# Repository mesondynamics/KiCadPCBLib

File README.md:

# KiCadPCBLib
PCB library for KiCad: custom symbols and footprints

Remember to set up [KiCadPCBLib3dmodels](https://github.com/mesondynamics/KiCadPCBLib3dmodels) for custom 3d models.

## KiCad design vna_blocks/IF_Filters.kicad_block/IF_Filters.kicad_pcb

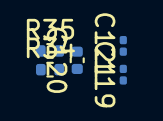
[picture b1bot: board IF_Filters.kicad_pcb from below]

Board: 8 copper layers, 5 parts (5 on the bottom side), 3 nets, no tracks yet.

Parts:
C119, C121: 10p; C_0201_0603Metric
C120: 27p; C_0402_1005Metric
R34, R35: 49.9; R_0402_1005Metric

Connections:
/RCVR1_IFF_N: C120.2, C121.1, R35.2
/RCVR1_IFF_P: C119.2, C120.1, R34.2
GNDA: C119.1, C121.2

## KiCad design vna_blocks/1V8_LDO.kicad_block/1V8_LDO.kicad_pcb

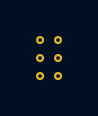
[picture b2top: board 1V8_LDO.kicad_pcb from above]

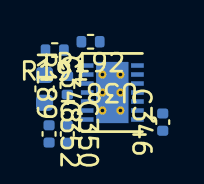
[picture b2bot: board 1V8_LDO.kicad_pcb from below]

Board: 8 copper layers, 8 parts (8 on the bottom side), 5 nets, no tracks yet.

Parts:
C346, C350, C352: 10u; C_0402_1005Metric
C348: 4.7u; C_0603_1608Metric
R189: 18k; R_0402_1005Metric
R191: 43k; R_0402_1005Metric
R192: 10k; R_0402_1005Metric
U38: LT3041ADE-PBF; 05-08-1708_ADI-L

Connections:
/1V8ADC1: C350.1, C352.1, R191.2, U38.12 (OUTS), U38.13 (OUT), U38.14 (OUT)
/Power/1V8/PGFB_1V8ADC1: R191.1, R192.2, U38.8 (PGFB)
/Power/3V8_int: C346.2, U38.1 (IN), U38.2 (IN), U38.3 (IN)
GNDA: C346.1, C348.2, C350.2, C352.2, R189.1, R192.1, U38.10 (GND), U38.11 (GND), U38.15 (GND)
unnamed: C348.1, R189.2, U38.9 (SET)

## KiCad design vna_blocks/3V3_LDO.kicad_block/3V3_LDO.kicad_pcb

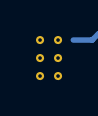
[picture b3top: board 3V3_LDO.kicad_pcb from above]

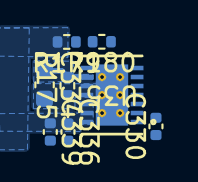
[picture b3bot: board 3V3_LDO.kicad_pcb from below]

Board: 8 copper layers, 8 parts (8 on the bottom side), 5 nets.

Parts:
C330, C336, C339: 10u; C_0402_1005Metric
C334: 4.7u; C_0603_1608Metric
R175: 33.2k; R_0402_1005Metric
R179: 89k; R_0402_1005Metric
R180: 10k; R_0402_1005Metric
U35: LT3041ADE-PBF; 05-08-1708_ADI-L

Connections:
/3V3_Synth: C336.1, C339.1, R179.2, U35.12 (OUTS), U35.13 (OUT), U35.14 (OUT)
/Power/3V3/PGFB_3V3Synth: R179.1, R180.2, U35.8 (PGFB)
GNDA: C330.1, C334.2, C336.2, C339.2, R175.1, R180.1, U35.10 (GND), U35.11 (GND), U35.15 (GND)
unnamed: C330.2, U35.1 (IN), U35.2 (IN), U35.3 (IN)
unnamed: C334.1, R175.2, U35.9 (SET)

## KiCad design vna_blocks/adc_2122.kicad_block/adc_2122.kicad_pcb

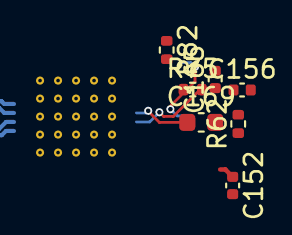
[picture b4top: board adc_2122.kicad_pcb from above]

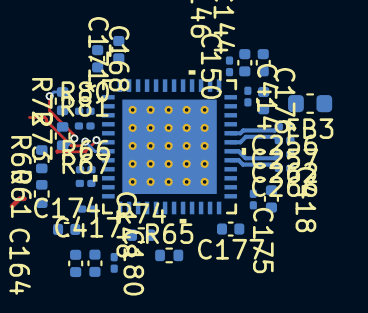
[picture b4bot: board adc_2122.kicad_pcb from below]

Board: 8 copper layers, 38 parts (31 on the bottom side), 24 nets.

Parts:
C144: 10u; C_0402_1005Metric
C146: 1u; C_0402_1005Metric
C148, C152, C156, C164, C165, C168, C171, C174, C175, C176, C177: 0.1u; C_0402_1005Metric
C150, C180, C414, C417, C418: 10p; C_0201_0603Metric
C169: 2.2u; C_0603_1608Metric
C256, C257, C262, C266: 0.1u; C_0201_0603Metric
FB3: MPZ1608S601ATA00; L_0603_1608Metric
R60, R61, R72, R73: 200; R_0402_1005Metric
R62, R75: 10; R_0402_1005Metric
R65, R74: 100; R_0402_1005Metric
R66, R67, R80, R81: 5; R_0201_0603Metric
R82: 1k; R_0402_1005Metric
U15: LTC2122IUK-TRPBF; QFN-48_UK_LIT-L

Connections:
/1V8_IO: C175.1, C176.1, C414.1, C418.1, U15.25 (OVDD), U15.26 (OVDD), U15.35 (OVDD), U15.36 (OVDD)
/ADC1_CLK_N: R74.2, U15.16 (DEVCLK+)
/ADC1_CLK_P: R74.1, U15.15 (DEVCLK-)
/Detector_adc_stage/1V8A_ADC1: C144.1, C146.1, C148.1, C150.1, C164.2, C168.2, C171.1, C174.2, C177.2, C180.1, C417.1, FB3.2, R82.1, U15.1 (VDD), U15.12 (VDD), U15.13 (VDD), U15.23 (VDD), U15.24 (VDD), U15.37 (VDD), U15.38 (VDD), U15.48 (VDD)
/Detector_adc_stage/A+: C256.2, U15.32 (CMLOUT_A0+)
/Detector_adc_stage/A-: C257.2, U15.31 (CMLOUT_A0-)
/Detector_adc_stage/B+: C262.2, U15.30 (CMLOUT_B0+)
/Detector_adc_stage/B-: C266.2, U15.29 (CMLOUT_B0-)
/Detector_adc_stage/SENSE: R82.2, U15.5 (SENSE)
/Detector_adc_stage/V_CM1: C165.1, R62.2, R75.2, U15.7 (VCM)
/RCVR1_IFF_N: R60.1, R66.1
/RCVR1_IFF_P: R61.2, R67.1
/RCVR1_IFR_N: R72.1, R80.1
/RCVR1_IFR_P: R73.2, R81.1
/SYSREF1_N: R65.2, U15.19 (SYSREF-)
/SYSREF1_P: R65.1, U15.18 (SYSREF+)
GNDA: C144.2, C146.2, C148.2, C150.2, C152.2, C156.2, C164.1, C165.2, C168.1, C169.2, C171.2, C174.1, C175.2, C176.2, C177.1, C180.2, C414.2, C417.2, C418.2, U15.2 (GND), U15.8 (GND), U15.11 (GND), U15.14 (GND), U15.17 (GND), U15.20 (GND), U15.39 (GND), U15.40 (GND), U15.47 (GND), U15.49 (GND)
unnamed: C152.1, R60.2, R61.1, R62.1
unnamed: C156.1, R72.2, R73.1, R75.1
unnamed: R80.2, U15.3 (AINA+)
unnamed: R81.2, U15.4 (AINA-)
unnamed: R67.2, U15.10 (AINB+)
unnamed: R66.2, U15.9 (AINB-)
unnamed: C169.1, U15.6 (VREF)

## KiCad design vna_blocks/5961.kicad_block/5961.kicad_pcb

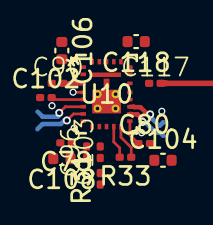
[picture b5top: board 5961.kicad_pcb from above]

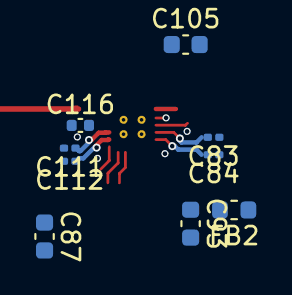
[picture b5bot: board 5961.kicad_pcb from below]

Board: 8 copper layers, 23 parts (9 on the bottom side), 17 nets.

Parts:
C78, C80: 100p; C_0201_0603Metric
C83, C84, C111, C112: 0.1u; C_0201_0603Metric
C87, C93, C105: 4.7u; C_0603_1608Metric
C90, C96, C103, C117: P21BNL300M5S; P21BN
C102: 100n; C_0201_0603Metric
C104, C106, C108: 1n; C_0402_1005Metric
C116, C118: 100n; C_0402_1005Metric
FB2: MPZ1608S601ATA00; L_0603_1608Metric
R31: 49.9; R_0201_0603Metric
R33: 100; R_0201_0603Metric
U10: ADL5961ACCZ; CC-26-2_ADI

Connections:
/1V8_IO: C118.2, U10.22 (OVDD)
/5V_RCVR2: C105.2, C106.2, FB2.1, U10.1 (AVCC)
/Front_end_receiver/2_6_N: C83.2, U10.6 (IFFM)
/Front_end_receiver/2_6_P: C84.2, U10.7 (IFFP)
/Front_end_receiver/2_15_N: C111.1, U10.16 (IFRM)
/Front_end_receiver/2_15_P: C112.1, U10.15 (IFRP)
/Front_end_receiver/5V_RCVR2_OVCC: C78.1, C80.1, C87.1, C93.1, C104.1, C108.1, FB2.2, U10.8 (OVCC), U10.14 (OVCC)
/Front_end_receiver/VCM: C116.2, U10.17 (VCM)
/f_OF2_N: R33.1, U10.13 (OFM)
/f_OF2_P: R33.2, U10.12 (OFP)
GNDA: C78.2, C80.2, C87.2, C93.2, C102.1, C104.2, C105.1, C106.1, C108.2, C116.1, C118.1, R31.1, U10.2 (AGND), U10.4 (AGND), U10.18 (AGND), U10.20 (AGND), U10.27 (EPAD), U10.28 (EPAD), U10.29 (EPAD)
unnamed: C103.1, R31.2
unnamed: C102.2, U10.5 (CAP)
unnamed: C103.2, U10.10 (LOM)
unnamed: C96.2, U10.9 (LOP)
unnamed: C90.2, U10.3 (RFIN)
unnamed: C117.1, U10.19 (RFOUT)

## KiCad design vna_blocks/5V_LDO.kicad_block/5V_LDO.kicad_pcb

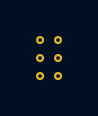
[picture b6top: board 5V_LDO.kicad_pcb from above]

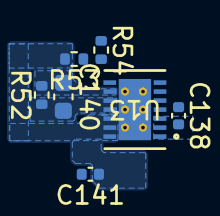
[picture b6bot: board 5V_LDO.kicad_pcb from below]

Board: 8 copper layers, 7 parts (7 on the bottom side), 5 nets, no tracks yet.

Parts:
C138, C141: 10u; C_0402_1005Metric
C140: 4.7u; C_0603_1608Metric
R52: 49.9k; R_0402_1005Metric
R53: 140k; R_0402_1005Metric
R54: 10k; R_0402_1005Metric
U13: LT3041ADE-PBF; 05-08-1708_ADI-L

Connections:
/5V_RCVR2: C141.1, R53.2, U13.12 (OUTS), U13.13 (OUT), U13.14 (OUT)
/Power/5V/+6V_int: C138.2, U13.1 (IN), U13.2 (IN), U13.3 (IN)
/Power/5V/PGFB_5VRCVR2: R53.1, R54.2, U13.8 (PGFB)
GNDA: C138.1, C140.2, C141.2, R52.1, R54.1, U13.10 (GND), U13.11 (GND), U13.15 (GND)
unnamed: C140.1, R52.2, U13.9 (SET)

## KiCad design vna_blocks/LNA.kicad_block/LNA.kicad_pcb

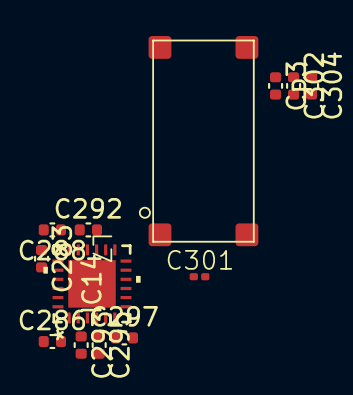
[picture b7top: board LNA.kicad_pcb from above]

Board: 4 copper layers, 13 parts (0 on the bottom side), 8 nets, no tracks yet.

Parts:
C283, C286, C288, C292, C293, C295, C297: 100n; C_0402_1005Metric
C301: P21BNL300M5S; P21BN
C302: 10n; C_0402_1005Metric
C304: 1u; C_0402_1005Metric
Cp3: 1p; C_0402_1005Metric
IC14: LVA-273PN+; DG1847_MNC-L
L7: BCR272JLC; BCR-272

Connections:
/5V: C286.2, C293.1, C302.1, C304.1, Cp3.1, IC14.1 (VC), IC14.3 (VB), L7.2
/LO_path/amp_out2: C301.1, IC14.10 (RF-OUT_&_VCC), L7.1
GNDA: C283.1, C286.1, C288.2, C292.2, C293.2, C295.2, C297.2, C302.2, C304.2, Cp3.2, IC14.9 (GND_1), IC14.11 (GND_2), IC14.21 (GND_3), IC14.23 (GND_4), IC14.25 (GND_5)
unnamed: C297.1, IC14.6 (CG1)
unnamed: C295.1, IC14.5 (CG2)
unnamed: C292.1, IC14.17 (CG3)
unnamed: C288.1, IC14.18 (CG4)
unnamed: C283.2, IC14.20 (CG5)

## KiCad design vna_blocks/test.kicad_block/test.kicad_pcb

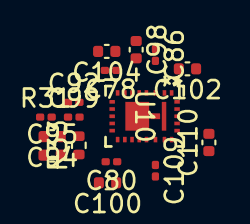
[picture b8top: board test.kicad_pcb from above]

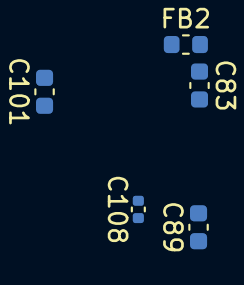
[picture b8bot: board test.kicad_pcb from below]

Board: 4 copper layers, 21 parts (5 on the bottom side), 13 nets, no tracks yet.

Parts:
C78, C80: 100p; C_0201_0603Metric
C83, C89, C101: 4.7u; C_0603_1608Metric
C86, C92, C99, C109: P21BNL300M5S; C_0201_0603Metric
C94, C95, C98, C108, C110: 100n; C_0402_1005Metric
C100, C102, C104: 1n; C_0402_1005Metric
FB2: MPZ1608S601ATA00; L_0603_1608Metric
R31: 49.9; R_0201_0603Metric
R33: 100; R_0402_1005Metric
U10: ADL5961ACCZ; CC-26-2_ADI

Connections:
/1V8D: C110.2, U10.22 (OVDD)
/5V_RCVR2: C101.2, C102.2, FB2.1, U10.1 (AVCC)
/Front_end_receiver/5V_RCVR2_OVCC: C78.1, C80.1, C83.1, C89.1, C100.1, C104.1, FB2.2, U10.8 (OVCC), U10.14 (OVCC)
/Front_end_receiver/VCM: C108.2, U10.17 (VCM)
GNDA: C78.2, C80.2, C83.2, C89.2, C98.1, C100.2, C101.1, C102.1, C104.2, C108.1, C110.1, R31.1, U10.2 (AGND), U10.4 (AGND), U10.18 (AGND), U10.20 (AGND), U10.27 (EPAD), U10.28 (EPAD), U10.29 (EPAD)
unnamed: C99.1, R31.2
unnamed: C98.2, U10.5 (CAP)
unnamed: C99.2, U10.10 (LOM)
unnamed: C92.2, U10.9 (LOP)
unnamed: C95.2, R33.1, U10.13 (OFM)
unnamed: C94.2, R33.2, U10.12 (OFP)
unnamed: C86.2, U10.3 (RFIN)
unnamed: C109.1, U10.19 (RFOUT)

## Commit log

2025-05-22 Update to KiCad9
2025-05-27 Add Power.kicad_sch REFCLK.kicad_sch etc.
2025-05-28 Add pmiao
2025-05-28 Reassign /pmiao/ for 3d models.
2025-05-28 Add FEP_V3_Castellated.
2026-02-20 first commit, vna project
2026-02-21 added some synthesizer parts for vna
2026-02-21 more VNA parts
2026-02-27 added components
2026-02-28 new models
2026-02-28 added some spice models
2026-02-28 removed file
2026-03-02 fixed CAP vs RFOUT symbol mislabelling on 5961
2026-03-03 added balun
2026-03-06 new additions
2026-03-10 fixed permissions
2026-03-11 added sym
2026-03-11 test
2026-03-12 added footprints
2026-04-01 updated parts
2026-04-02 design blocks
2026-04-02 new design blocks, footprints
2026-04-06 hmc7044 design block
2026-04-13 new parts, design blocks updated
2026-04-14 added BTM-0026 symbol and footprint
2026-04-14 new footprints
2026-04-15 added RF crossover
2026-04-20 added fmc connector io
2026-04-21 fmc connectors and mounting holes
2026-05-05 new parts
2026-05-29 fixed 50 ohm for coax port, fixed power blocks
2026-06-08 fixed IC courtyard issues
